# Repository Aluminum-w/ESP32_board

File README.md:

View this project on [CADLAB.io](https://cadlab.io/project/24975). 

# ESP32_board

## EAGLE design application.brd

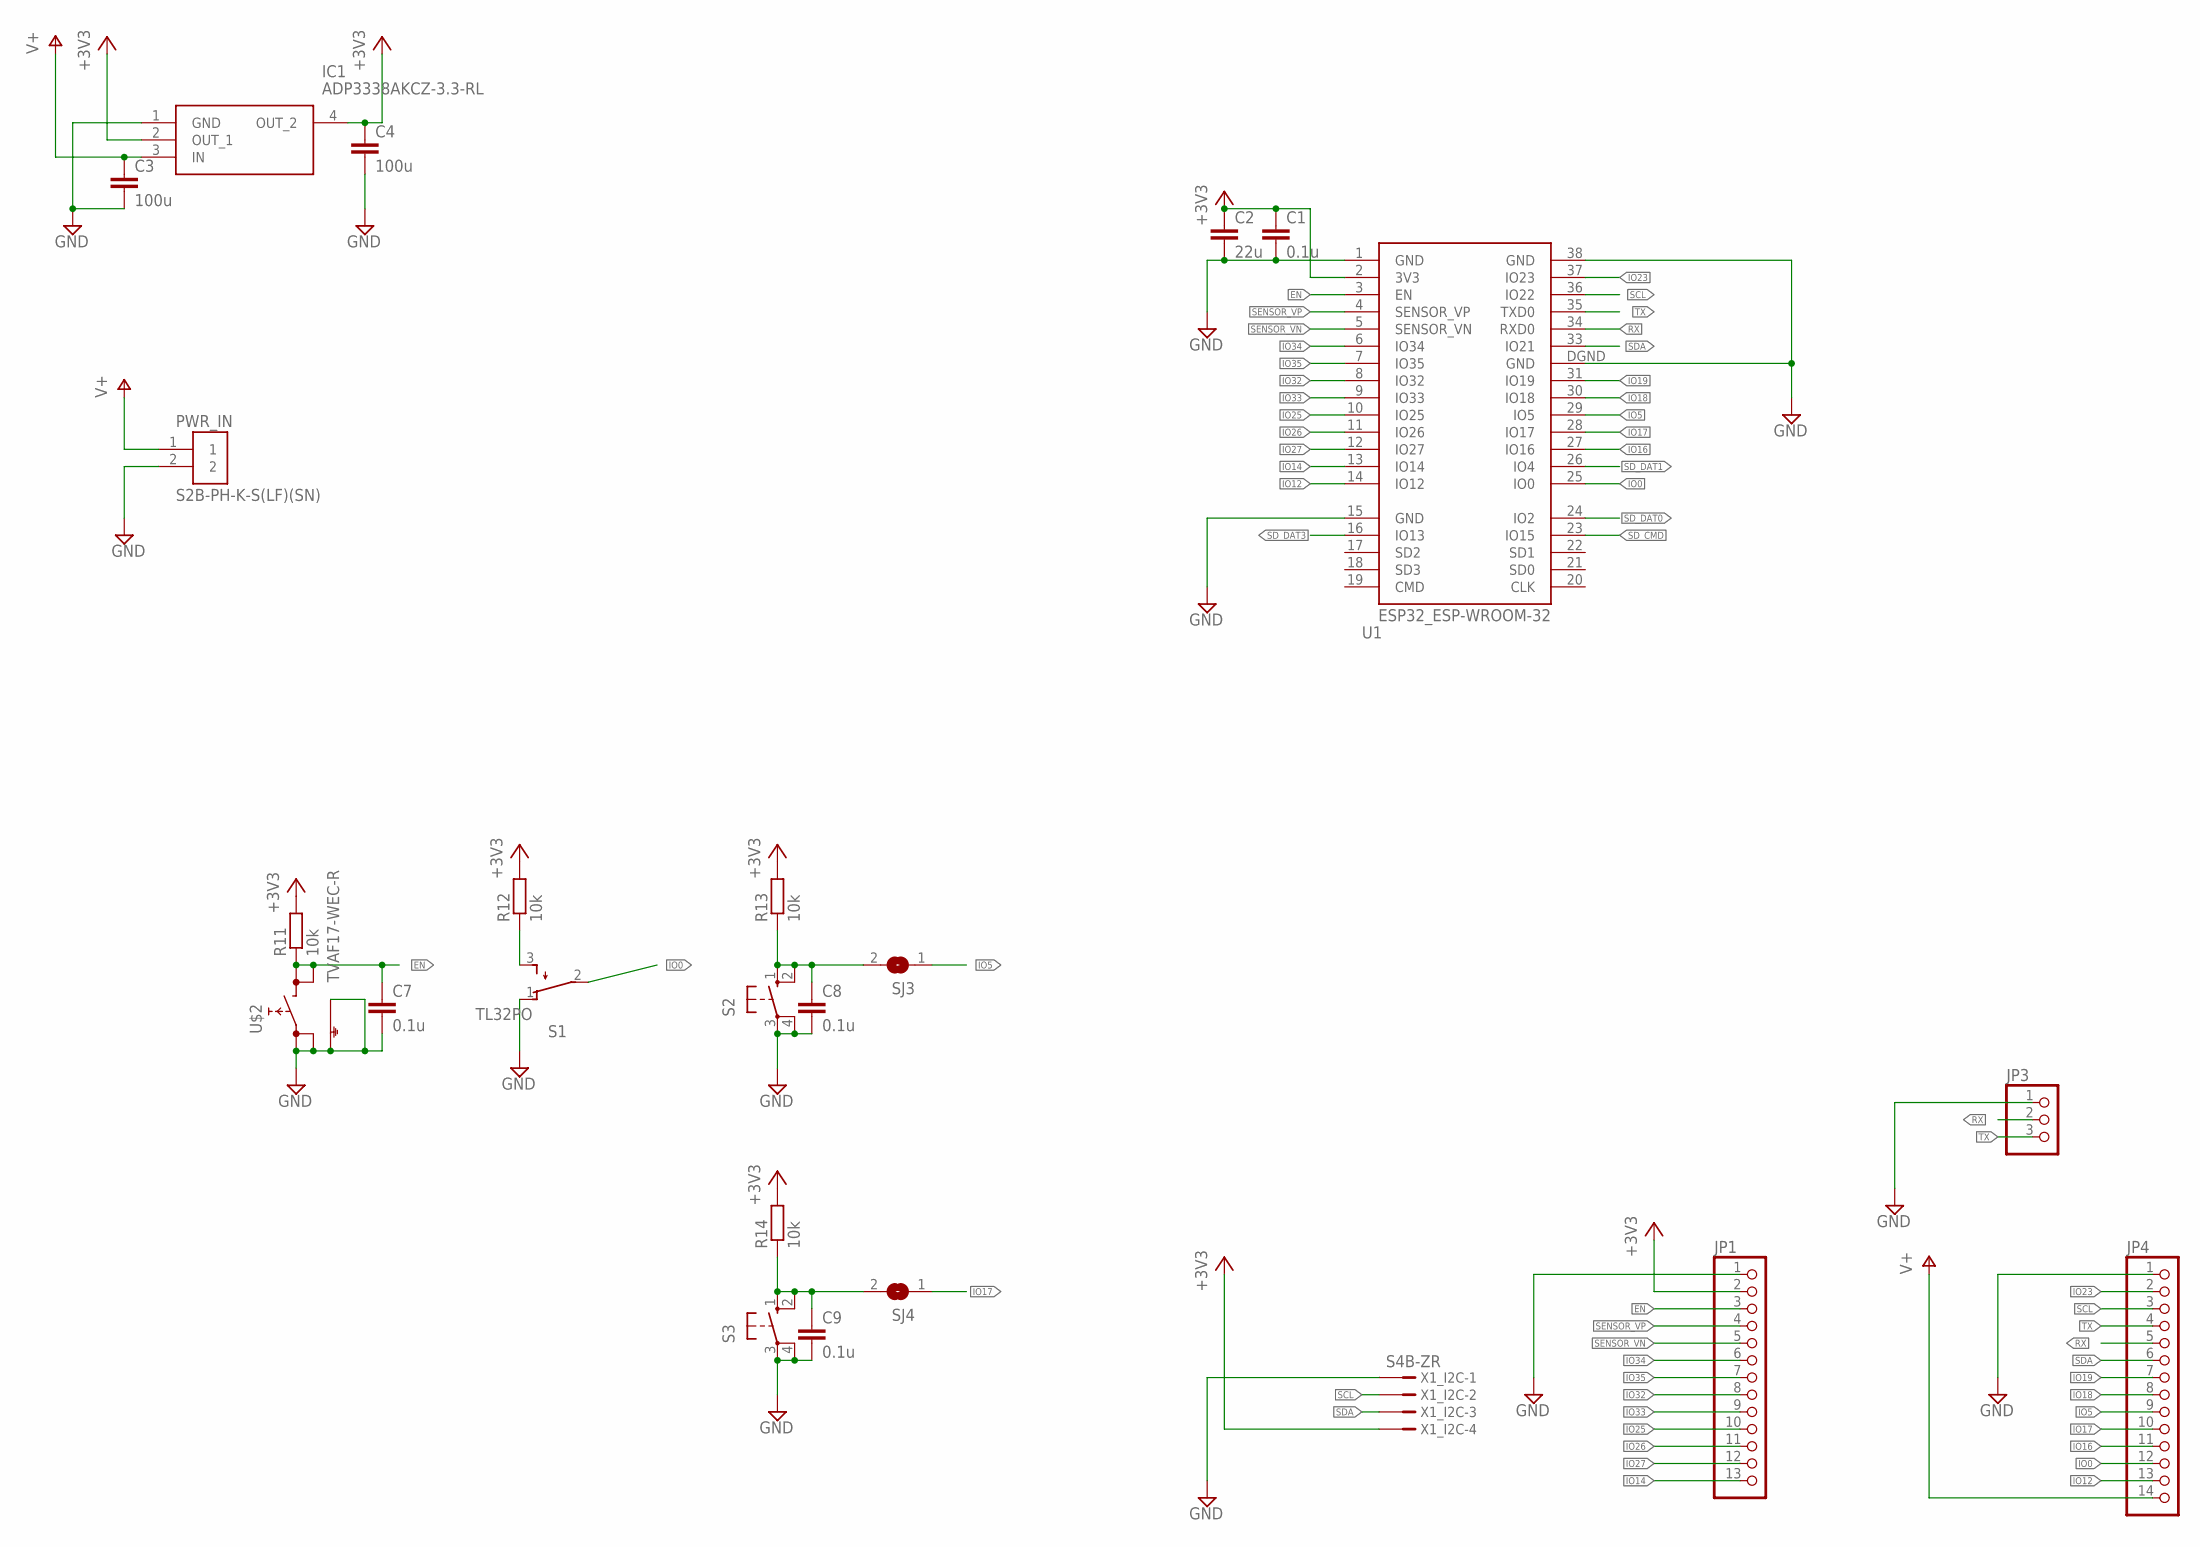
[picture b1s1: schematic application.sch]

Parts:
C1, C7, C8, C9: 0.1u; C0603K
C2: 22u; C0805
C3, C4: 100u; C1206
IC1: ADP3338AKCZ-3.3-RL; SOT230P700X180-4N
JP1: PINHD-1X13; 1X13
JP3: PINHD-1X3; 1X03
JP4: PINHD-1X14; 1X14
PWR_IN: S2B-PH-K-S(LF)(SN)
R11, R12, R13, R14: 10k; R0603
S1: TL32PO; TL3XPO
S2, S3: 10-XX; B3F-10XX
SJ3, SJ4: SJW
U1: ESP32_ESP-WROOM-32
U$2: TVAF17-WEC-R
X1_I2C: S4B-ZR

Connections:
+3V3: C1.1, C2.1, C4.1, IC1.2 (OUT_1), IC1.4 (OUT_2), JP1.2, R11.2, R12.2, R13.2, R14.2, U1.2 (3V3), X1_I2C.4
EN: C7.1, JP1.3, R11.1, U1.3 (EN), U$2.P$3 (3), U$2.P$4 (4)
GND: C1.2, C2.2, C3.2, C4.2, C7.2, C8.2, C9.2, IC1.1 (GND), JP1.1, JP3.1, JP4.1, PWR_IN.2, S1.1 (O), S2.3, S2.4 (P1), S3.3, S3.4 (P1), U1.1 (GND), U1.15 (GND), U1.38 (GND), U1.DGND (GND), U$2.P$1 (1), U$2.P$2 (2), U$2.P$5 (5), U$2.P$6 (6), X1_I2C.1
IO0: JP4.12, S1.2, U1.25 (IO0)
IO5: JP4.9, SJ3.1, U1.29 (IO5)
IO12: JP4.13, U1.14 (IO12)
IO14: JP1.13, U1.13 (IO14)
IO16: JP4.11, U1.27 (IO16)
IO17: JP4.10, SJ4.1, U1.28 (IO17)
IO18: JP4.8, U1.30 (IO18)
IO19: JP4.7, U1.31 (IO19)
IO23: JP4.2, U1.37 (IO23)
IO25: JP1.10, U1.10 (IO25)
IO26: JP1.11, U1.11 (IO26)
IO27: JP1.12, U1.12 (IO27)
IO32: JP1.8, U1.8 (IO32)
IO33: JP1.9, U1.9 (IO33)
IO34: JP1.6, U1.6 (IO34)
IO35: JP1.7, U1.7 (IO35)
unnamed: C8.1, R13.1, S2.1 (S), S2.2 (S1), SJ3.2
unnamed: C9.1, R14.1, S3.1 (S), S3.2 (S1), SJ4.2
unnamed: R12.1, S1.3 (S)
RX: JP3.2, JP4.5, U1.34 (RXD0)
SCL: JP4.3, U1.36 (IO22), X1_I2C.2
SDA: JP4.6, U1.33 (IO21), X1_I2C.3
SD_CMD: U1.23 (IO15)
SD_DAT0: U1.24 (IO2)
SD_DAT1: U1.26 (IO4)
SD_DAT3: U1.16 (IO13)
SENSOR_VN: JP1.5, U1.5 (SENSOR_VN)
SENSOR_VP: JP1.4, U1.4 (SENSOR_VP)
TX: JP3.3, JP4.4, U1.35 (TXD0)
V+: C3.1, IC1.3 (IN), JP4.14, PWR_IN.1

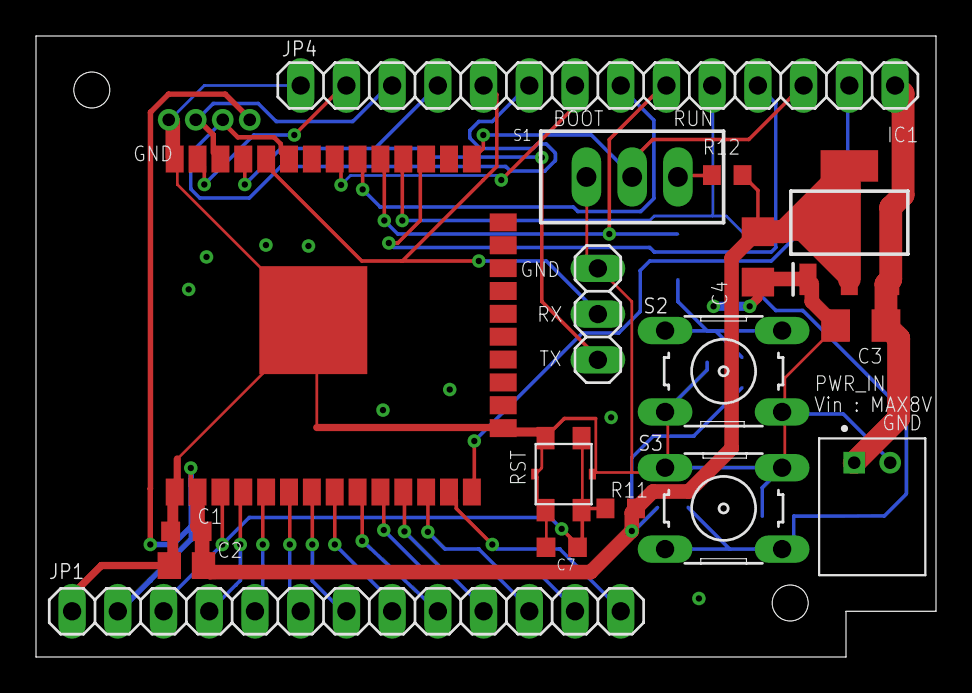
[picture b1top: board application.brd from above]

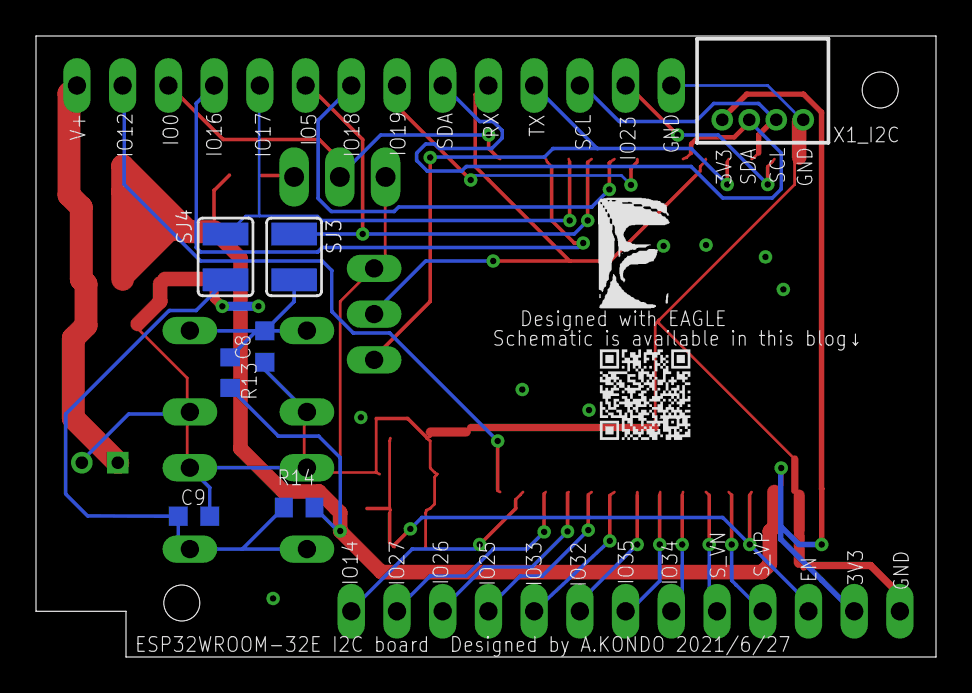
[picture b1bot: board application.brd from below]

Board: 2 copper layers, 50.0 x 34.5 mm, 24 parts (7 on the bottom side), 29 nets.

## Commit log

2021-12-03 ESP32 board ver.1
2021-12-03 Backlink to CADLAB.io has been added.
